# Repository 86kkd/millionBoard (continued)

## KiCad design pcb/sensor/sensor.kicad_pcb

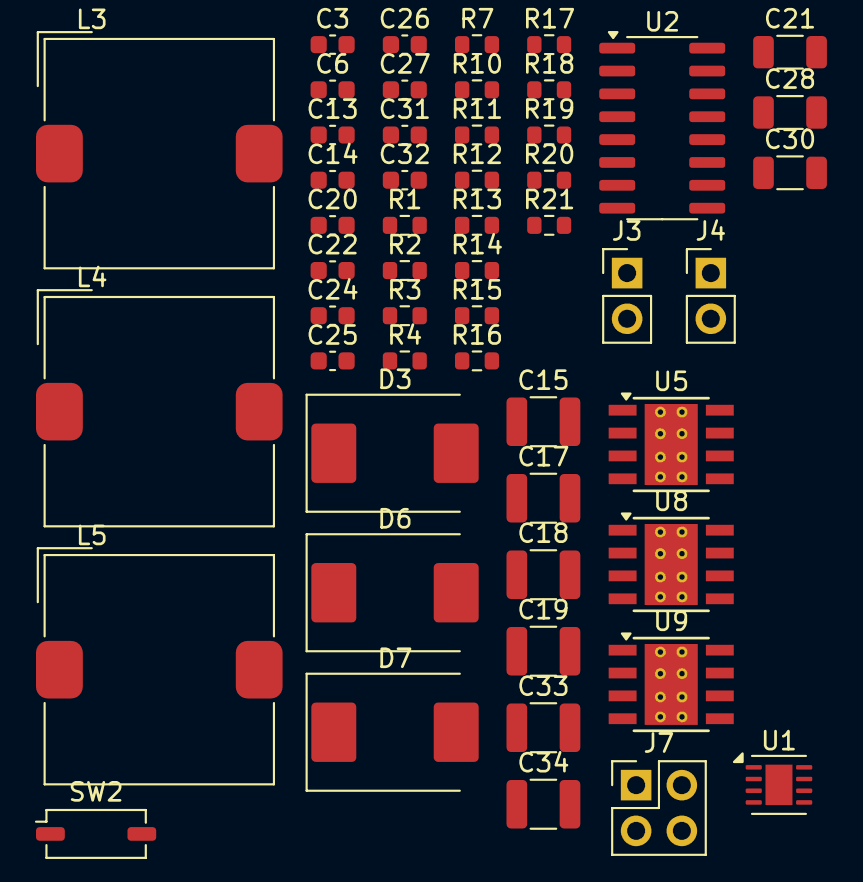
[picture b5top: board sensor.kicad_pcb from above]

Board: 2 copper layers, 53 parts (0 on the bottom side), 36 nets, no tracks yet.

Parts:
C3: 0.1uF; C_0603_1608Metric
C6: 10uF; C_0603_1608Metric
C13, C25, C32: 100nF/16v; C_0603_1608Metric
C14: 68nF; C_0603_1608Metric
C15, C17: 10uF/35v; C_1210_3225Metric
C18, C19: 10uf/50v; C_1210_3225Metric
C20, C22: 100nf/50v; C_0603_1608Metric
C21, C28, C30: 4.7uf/50v; C_1206_3216Metric
C24, C31: 47nF; C_0603_1608Metric
C26, C27: 10uF/10v; C_0603_1608Metric
C33, C34: 10uF/16v; C_1210_3225Metric
D3, D6, D7: B560C; D_SMC
J3: sig_in; PinHeader_1x02_P2.54mm_Vertical
J4: sig_out; PinHeader_1x02_P2.54mm_Vertical
J7: Conn_02x02_Counter_Clockwise; PinHeader_2x02_P2.54mm_Vertical
L3, L4: 22uH; L_TDK_SLF12565
L5: 47uH; L_TDK_SLF12565
R1: 300k; R_0603_1608Metric
R2, R3: 100; R_0603_1608Metric
R4, R10, R14, R18: 10k; R_0603_1608Metric
R7: 100k; R_0603_1608Metric
R11, R15: 62k; R_0603_1608Metric
R12: 33k; R_0603_1608Metric
R13: 1k; R_0603_1608Metric
R16: 56k; R_0603_1608Metric
R17: 680; R_0603_1608Metric
R19, R20: 1.3k; R_0603_1608Metric
R21: 120; R_0603_1608Metric
SW2: SW_SPST; SW_DIP_SPSTx01_Slide_Copal_CHS-01A_W5.08mm_P1.27mm_JPin
U1: SIT1042AQT/3; DFN-8-1EP_3x3mm_P0.65mm_EP1.5x2.25mm
U2: HX711; SOP-16_3.9x9.9mm_P1.27mm
U5, U8, U9: LMR16030SDDAR; TI_SO-PowerPAD-8_ThermalVias

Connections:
3.3V/3A: C25.1, C26.1, C27.2, L4.2, R12.1
5V/3A: C32.1, C33.1, C34.2, L5.2, R16.1
24V/3A: C13.1, C15.1, C17.2, C21.2, C22.1, C28.1, C30.2, L3.2, R1.1, U8.2 (VIN), U9.2 (VIN)
+3.3V: C6.2, J7.1, U1.5 (VIO), U2.15 (RATE), U2.16 (DVDD)
+5V: J7.2, U1.3 (VCC), U2.1 (VSUP), U2.3 (AVDD)
CANH: SW2.2 (B), U1.7 (CANH)
CANL: R21.2, U1.6 (CANL)
DOUT: J4.1, U2.12 (DOUT)
GND: C6.1, C14.2, C15.2, C17.1, C18.2, C19.1, C20.2, C21.1, C22.2, C24.2, C26.2, C27.1, C28.2, C30.1, C31.2, C33.2, C34.1, D3.2 (A), D6.2 (A), D7.2 (A), J7.3, J7.4, R4.2, R7.2, R14.2, R18.2, R19.2, R20.2, U1.2 (GND), U1.8 (STB), U2.4 (VFB), U2.5 (AGND), U2.14 (XI), U5.7 (GND), U5.9 (EP), U8.7 (GND), U8.9 (EP), U9.7 (GND), U9.9 (EP)
INA+: J3.2, R2.2
INA-: J3.1, R3.2
unnamed: D3.1 (K), L3.1, U5.8 (SW)
unnamed: D6.1 (K), L4.1, U8.8 (SW)
unnamed: D7.1 (K), L5.1, U9.8 (SW)
unnamed: R1.2, R10.1
unnamed: R11.2, R19.1
unnamed: R12.2, R13.1
unnamed: R15.2, R20.1
unnamed: R16.2, R17.1
unnamed: R21.1, SW2.1 (A)
unnamed: C3.1, R2.1, U2.8 (INA+)
unnamed: C3.2, R3.1, U2.7 (INA-)
unnamed: C13.2, U5.1 (BOOT)
unnamed: R4.1, R10.2, U5.5 (FB)
unnamed: R7.1, U5.4 (RT/YNC)
unnamed: C14.1, U5.6 (SS/PGOOD)
unnamed: C25.2, U8.1 (BOOT)
unnamed: R13.2, R14.1, U8.5 (FB)
unnamed: R11.1, U8.4 (RT/YNC)
unnamed: C24.1, U8.6 (SS/PGOOD)
unnamed: C32.2, U9.1 (BOOT)
unnamed: R17.2, R18.1, U9.5 (FB)
unnamed: R15.1, U9.4 (RT/YNC)
unnamed: C31.1, U9.6 (SS/PGOOD)
PD_SCK: J4.2, U2.11 (PD_SCK)
VIN_MAX60V: C18.1, C19.2, C20.1, U5.2 (VIN)

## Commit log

2024-09-26 init
2024-11-24 restruce project
2024-12-04 add simpleFoc submodule
2024-12-04 foc subBoard design
2024-12-04 update foc board
2024-12-04 foc debug info designe
2024-12-05 assign foot prints
2024-12-10 更新原理图和pcb
2024-12-17 focV3 update
2024-12-19 foc example code
2024-12-23 dc-dc 原理图
2024-12-24 update dc-dc
2024-12-24 update foc ctrl code
2024-12-24 update pcb
2024-12-24 update foc pcb
2024-12-24 update sensor
2024-12-25 update hx711 sersor src
2024-12-25 update gitingore
2025-01-09 更新kiacad sensor的原理图
2025-01-28 can logic
2025-01-30 udpate twai api version
2025-01-31 more check
2025-01-31 最简实现-faile
2025-02-25 feat: update sensor pcb
2025-02-25 feat: update can code
2025-02-25 feat: update foc ctrl
2025-02-25 feat: update gitignore
2025-02-27 feat: backup
2025-03-03 feat: update dc-dc
2025-03-03 feat: update foc
2025-03-04 feat: add dc-dc compute script
2025-03-04 feat: add can test script
2025-03-04 feat: update sch adn scripts
2025-03-08 feat: update
2025-03-08 feat: update ignore
2025-03-11 feat: update pdf
2025-04-07 success config
2025-04-07 feat: restruce project
2025-04-07 feat: compaile success
2025-04-08 feat: update default comfig
2025-04-09 feat: add component enable
2025-04-09 feat: error config component
2025-04-09 feat: fix error component enable
2025-04-09 feat: fix component error
2025-04-09 feat: fix enable component bug
2025-04-09 feat: add double motor ctl
2025-04-09 feat: fix motor enale pin
2025-04-10 feat: add current sensor for motor
2025-04-20 feat: add pressure_sensor implement
2025-05-01 feat: add new dc-dc
2025-05-02 feat: new_dc-dc pcb
2025-05-02 feat: update reade nvs logic
2025-05-02 fix: make eable component logic applay for all xtask
2025-05-02 feat: add more designe detail
2025-05-02 feat: udpate pcb
2025-05-02 feat: using cpp for the project
2025-05-02 refactor: internal pressure_sensor init logic
2025-05-02 chore: update kicad_sch
2025-05-02 chore: update foc ctrl pin
2025-05-14 feat: update a lot
2025-05-14 feat: add nfc and gps depandency
2025-05-14 feat: udpate nfc
2025-05-19 feat: add gps and nfc logic
2025-05-20 feat: 实现olcd显示
2025-05-20 feat: finish
